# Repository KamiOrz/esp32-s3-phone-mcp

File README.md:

# ESP32-S3 Phone MCP

[English](README.en.md) · [硬件工程](pcb-integrated/README.md) · [MIT License](LICENSE)

**让视觉 AI 通过 Wi-Fi 查看并操作安卓手机。** ESP32-S3 通过 USB ADB 连接手机，在设备上提供带鉴权的 MCP 服务；电脑或云端的多模态 AI 负责理解截图、决定操作，S3 负责执行。

手机无需安装额外应用，需要开启 USB 调试并授权设备。正常操作不依赖电脑上的 ADB 服务，也不依赖单独的 OCR 服务。

## 实拍：已验证的开发板原型

上图是已实测的 **YD-ESP32-23 / ESP32-S3 N16R8 开发板原型**，并非下方集成 PCB 的实物。手机便签中的产品介绍由原型操作输入。照片已移除 EXIF 等元数据。

## 集成 PCB 效果图

- ESP32-S3-WROOM-1-N16R8，独立 CP2102N USB 烧录串口。
- 一个 Type-C 母座接电脑/供电，一个 USB-A 母座接手机，所有焊接引脚为 SMT。
- 55×35mm、四层 PCB，四角 Ø2.2mm M2 固定孔，孔中心距49×29mm。
- 含模组天线伸出部分，组件平面包络约55×41.5mm；外壳还需预留装配和射频净空。
- 输入保护、Type-C 供电能力检测、3.3V 降压与手机端限流保护。

**集成板尚未打样或实板验证。** 当前原理图 ERC、PCB DRC 和一致性检查通过，未连接项为0；这不代表已完成 USB 阻抗、供电浪涌、温升和射频验证。部分3D元件使用简化外形，不能作为精密外壳公差依据。现有固件已在开发板验证，集成板仍需 CC/VBUS 板级适配。未发布制造放行 Gerber。

[KiCad 工程](pcb-integrated/phone-mcp-s3.kicad_pro) · [PCB](pcb-integrated/phone-mcp-s3.kicad_pcb) · [原理图 PDF](pcb-integrated/review/phone-mcp-s3-schematic.pdf) · [BOM](pcb-integrated/BOM.csv) · [检查报告](pcb-integrated/review/STATUS.md)

## 工作原理

```mermaid
flowchart LR
    AI[电脑或云端的视觉 AI] -->|MCP / Wi-Fi| S3[ESP32-S3\n鉴权与命令执行]
    S3 -->|USB Host / ADB| Phone[已授权 USB 调试的安卓手机]
    Phone -->|截图 PNG| S3
    S3 -->|MCP 图片内容| AI
```

截图通过 Wi-Fi 返回给 AI，不经过低速串口。AI 根据截图确定控件位置，调用点击、滑动或应用命令，再截图确认结果。ADB 授权身份在 S3 上使用，每台设备应生成自己的密钥。

## 支持的操作

| 能力 | MCP 工具示例 |
|---|---|
| 查看屏幕与状态 | `phone_screenshot`、`phone_status`、`phone_device_info` |
| 点击、滑动、长按、按键 | `phone_tap`、`phone_swipe`、`phone_long_press`、`phone_keyevent` |
| 应用管理 | `phone_list_apps`、`phone_launch_app`、`phone_stop_app`、`phone_foreground_app` |
| 命令和界面信息 | `phone_adb_shell`、`phone_ui_hierarchy`、`phone_app_info` |
| 唤醒、输入 | `phone_wake_screen`、`phone_input_password`、`phone_input_text` |
| 打开链接 | `phone_open_url` |

当前 MCP 0.4.0 共19个工具。数字 PIN 输入用于输入已知的正确密码，不绕过锁屏；普通文本输入目前仅支持可打印 ASCII。完整参数、返回结构和限制见 [技术说明](README.en.md)。

## 开始使用开发板原型

1. 准备 ESP32-S3 N16R8 开发板、数据线、可用的 USB Host 供电路径，以及已开启 USB 调试的安卓手机。
2. 安装并启用 ESP-IDF 6.1 环境。安卓 platform-tools 仅在本地生成独立 ADB 密钥时需要。
3. 克隆项目并生成本地配置：

```sh
git clone https://github.com/KamiOrz/esp32-s3-phone-mcp.git
cd esp32-s3-phone-mcp
python3 configure_local.py --url http://BOARD_IP/mcp
```

配置脚本交互式读取 Wi-Fi 信息，生成独立 ADB 密钥和 MCP 令牌；配置与密钥文件由 Git 忽略，不会写入公开仓库。

4. 编译烧录（替换串口名）：

```sh
bash hub-probe/build.sh -p /dev/cu.usbserial-PORT -b 460800 build flash
```

5. 在手机上授权设备的 USB 调试请求，然后使用 MCP 客户端连接 `http://BOARD_IP/mcp`，请求头携带 `Authorization: Bearer <本机令牌>`。

命令行测试：

```sh
python3 -m venv .venv
.venv/bin/pip install -r client-requirements.lock.txt
.venv/bin/python phone_cli.py --list
.venv/bin/python phone_cli.py phone_screenshot
.venv/bin/python phone_cli.py phone_launch_app --args '{"package":"com.coloros.calculator"}'
```

开发板的 USB-C 接口不一定支持向手机供电。原型使用板级 USB-OTG 供电改动和 USB Hub，接线应先核对具体开发板的 CC/VBUS 电路；不要把两个电源直接并联。详见[原型接线说明](README.en.md#current-hardware--wiring)。

## 适合什么场景

手机需要离开电脑、固定摆放或通过网络被 AI 调用时，S3 可以作为常驻控制节点。手机就在电脑旁边时，电脑直接连接 ADB 通常更快、功能也更完整。本项目不在 S3 上运行视觉大模型，不提供实时视频流，也不是完整桌面 ADB 的替代品。

当前服务使用局域网 HTTP 和令牌鉴权；不要将手机控制端口直接暴露到公网。手机截图、运行日志、PIN、Wi-Fi 密码和 ADB 私钥都应留在本地。见 [本地数据说明](LOCAL_DATA.md)。

## 目录与许可

- `hub-probe/`：ESP-IDF 固件，USB Host、ADB 与 MCP HTTP 服务。
- `phone_cli.py`、`wifi_client.py`：电脑端调用与截图测试客户端。
- `pcb-integrated/`：KiCad 原理图、PCB、BOM、渲染图和检查报告。
- `docs/images/`：项目实拍图。

原创代码、硬件设计和项目文档/图片按 [MIT](LICENSE) 许可发布，允许按许可证使用、修改与分发。第三方组件保留各自许可证，见 [第三方说明](THIRD_PARTY_NOTICES.md)。

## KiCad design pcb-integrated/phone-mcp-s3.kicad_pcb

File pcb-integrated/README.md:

# Phone MCP S3 集成板 — Rev A1 四层 PCB 评审包

状态：布局与布线完成，含四角 M2 固定孔。原理图 ERC、PCB DRC 与一致性检查通过，未连接为 0。尚未实板验证，不是制造放行版，未输出 Gerber。
目标：替代 YD-ESP32-23 开发板及 Hub，单机连接一台已授权 USB 调试的安卓手机。
用户已确认：ESP32-S3 模组、一个电脑 Type-C 母座、一个手机 USB-A 母座、全贴片焊接。
本目录独立于被忽略的 hardware/，不含网络密码、ADB 私钥、令牌、PIN 或手机数据。

## 1. 架构

```text
现有：电脑 → 开发板 COM         拟设计：电脑 → J1 Type-C
              │                                  ├─USB2 D±→ESD→U2 CP2102N→UART0→U1
          S3 开发板                               ├─CC1/2→U3 TUSB320LAI→供电能力状态→U1
              │                                  └─VBUS→输入保护→5V_SYS
          Hub → 手机                                              ├─U4 Buck→3V3→U1等
                                                                  └─U5 限流/反向保护→J2 VBUS
                                           U1 原生USB GPIO19/20→ESD→J2 USB-A→手机
```

U1：ESP32-S3-WROOM-1-N16R8，保持现有 16MB Flash / 8MB PSRAM 配置。
USB Host 与电脑 USB 串口为两条独立的数据通道，禁止并联。
J2 D+/D- 不短接，不做充电专用口，不宣告快充。
首版不做 PD 高压请求；输入目标是 5V。

## 2. 供电约束与默认策略

电脑端 Type-C 插座不代表电脑必然提供 1.5A/3A。
U3 固定为 UFP/Sink，读取上游默认/1.5A/3A 宣告；不得再并联固定 Rd。
U5 EN 硬件下拉，上电、复位、未读到可靠供电能力时手机 VBUS 关闭。
首版手机端预算目标 500mA，连同主板留出余量，只在检测到至少 1.5A
Type-C 宣告、输入电压正常且固件准备好时使能。
不能把限流典型值当成保证值：需根据 TPS2553 限流上下限选择 RILIM，
当前手机支路 RILIM=44.2kΩ/1%，按厂家公式计算阈值约 531.8–658.8mA，支持500mA正常负载。
输入 eFuse 的 RILM=1.62kΩ/1%，典型阈值约1.25A。仍需验证短路、浪涌、手机电容与线损。
默认电流的老电脑 A 口首先用于刷机/调试；不保证可同时带手机。
USB 枚举前、挂起、掉电等功耗约束仍需在硬件/固件联调验证；
CC 检测本身不等于 USB 枚举授权，不作为 USB 合规结论。

输入保护须落实过压截止/电流限制与输入电容量约束，不能仅靠 TVS
代替过压保护，也不能把所有大电容直接挂在未受控输入 VBUS。
U5 只保护手机支路，不能代替整个板子的输入保护。
5V_SYS 与 PHONE_VBUS 分网；USB-A 端反向灌电不得回到电脑。

## 3. 模组连接分配（已与 KiCad 导出网表核对）

| 功能 | U1 信号 | 说明 |
|---|---|---|
| 手机 USB D- | GPIO19 | 串联阻值按官方指南/实测，靠模组 |
| 手机 USB D+ | GPIO20 | USB Full Speed 12Mbps，成对走线 |
| 烧录 UART TX | GPIO43/U0TXD | 接 U2 RXD |
| 烧录 UART RX | GPIO44/U0RXD | 接 U2 TXD，3.3V 逻辑 |
| 自动下载/复位 | GPIO0、EN | U2 DTR/RTS 经互锁双 NPN 电路；另保留 SMT BOOT/RESET |
| 手机电源开关 | GPIO4 | EN 下拉，启动默认关闭 |
| 手机过流故障 | GPIO5 | 开漏故障输入，3.3V 上拉 |
| CC I2C SDA/SCL | GPIO8/GPIO9 | 3.3V 上拉，确认 U3 上电时序/电平兼容 |
| 状态 LED | GPIO10 | 普通 LED 与串联限流电阻 |
| 预留检测 | GPIO6/GPIO7 | 输入/输出电压分压，防止掉电反供 |

不使用 GPIO35/36/37 等可能被 octal PSRAM 占用的脚。
EN 上拉、复位 RC、GPIO0 上拉与其他启动脚按模组资料审查。
保留 3V3/GND/EN/IO0/TX/RX、两侧 D±、5V_SYS/PHONE_VBUS 测试焊盘。

## 4. 初步机械约束

板框 55×35mm，两接口同侧且开口对齐板边。四角 H1–H4 为 Ø2.2mm NPTH，孔中心距板边3mm、中心距49×29mm；螺丝头按Ø5mm预留双面及内层铜/走线避让。
模组天线位于相对一边，已外伸板边约6.5mm；组件总平面包络因此约55×41.5mm，不能把55×35mm当外壳内尺寸。外壳对应区域不得有金属/电池/螺柱。
模组天线实际禁布范围以官方封装与装壳射频验证为准。
最终改为4层、目标厚度1.6mm FR4：F.Cu为元件/信号及地铜，In1.Cu以GND为主，In2.Cu为信号，B.Cu为信号。In1有一处UART_RST_N局部跨线；需要在板厂叠层确认后进一步复核USB回流与该处地铜连续性。四层制板费用与两层不同。
USB 阻抗按板厂实际叠层计算，不能预先随意指定线宽/间距。
器件尽量顶面贴装；电阻电容以0603为主，QFN/DFN器件采用回流焊。
定位孔、安装孔和过孔可以存在；全贴片指所有焊接引脚（含接口固定脚）为SMT。
外壳需承受USB插拔力，不让固定焊盘单独承力。

## 5. 全贴片器件初选

当前清单见 BOM.csv；BOM-candidates.csv 是最早的选型草案，不作为装配依据。
J1=USB4110-GF-A、J2=UJ2-AH-4-SMT-TR，已依据厂家图核对为全SMT焊接，
J2自建封装的两个1.3mm孔是塑料定位柱孔，不是焊接脚。
L1=XGL4020-472MEC，4.7uH，10%/20%/30%电感下降对应1.9/3.0/4.1A；
C23=T520D157M010ATE055，150uF/10V聚合物，正极接PHONE_VBUS。
U6=TPS259573DSGR，主动低电平OVLO型，不可直接换成同封装其他使能极性版本。
R/C等通用被动器件的具体采购品牌、直流偏压降容及供货仍需在装配BOM冻结时确认。
不能把库存库中“信号SMT、外壳THT”的USB-A母座当全贴片替代。

## 6. 固件影响

现有网络MCP、ADB与截图逻辑可以复用，但不是原固件原样烧录即可发布。
新增 board profile：启动读取CC、管理VBUS EN/故障、欠压关断、恢复状态机。
先检测供电再使能手机VBUS，最后启动USB Host；Wi-Fi状态服务不能无限等待USB枚举，
供电不足时也应能够报告状态。电脑USB默认电流模式需结合CP2102N配置与SUSPEND管脚，
核对枚举前电流、总线电流描述符和挂起策略；不能直接照搬现有固件启动顺序。
不再对USB错误无条件整板重启；电源切换应与USB Host状态同步。
保留本机独立ADB身份生成与本地配置，凭据不进入EDA文件或制造资料。

## 7. 放行检查

- 锁定全部精确MPN、封装焊盘、USB-A纯SMT版本和供货渠道。
- 核对官方参考电路、自动下载真值表与CP2102N VBUS检测分压。
- 电源预算、RILIM公差、输入保护、浪涌、挂起功耗、反灌审查。
- KiCad原理图/ERC、网表审查、PCB走线/DRC与原理图一致性。
- 输出装配图、BOM、坐标、Gerber、钻孔；审核前不称可直接生产。
- 实板验证烧录/Wi-Fi峰值/手机ADB/短路/掉电/重复插拔与连续运行。

## 8. 官方资料

- 模组：https://www.espressif.com/sites/default/files/documentation/esp32-s3-wroom-1_wroom-1u_datasheet_en.pdf
- 设计指南：https://docs.espressif.com/projects/esp-hardware-design-guidelines/en/latest/esp32s3/
- UART：https://www.silabs.com/documents/public/data-sheets/cp2102n-datasheet.pdf
- CP2102N VBUS：https://community.silabs.com/s/article/cp2102n-requires-a-voltage-divider-on-vbus?language=en_US
- CC：https://www.ti.com/lit/ds/symlink/tusb320lai.pdf
- 供电开关：https://www.ti.com/lit/ds/symlink/tps2553.pdf
- Buck：https://www.diodes.com/datasheet/download/AP63200-AP63201-AP63203-AP63205.pdf
- C口纯SMT：https://gct.co/files/info/gct-ionex-usb4110-product-release-booklet.pdf
- A口候选：https://www.sameskydevices.com/product/resource/uj2-ah-smt.pdf

## 9. 当前验证状态

已完成：90个原理图实例（含3个电源标志、4个安装孔）、41个功能网络、234个引脚分配独立核对。
原理图ERC：0错误/0警告；PCB最终DRC：0项违规、0项未连接；原理图一致性：0差异。
PCB有67个贴装器件、16个测试焊盘和4个安装孔；所有焊接引脚为SMT。
最终检查见 `review/final/`，当前文件哈希和机械尺寸见 `review/state.json`。
原有 `review/pcb-current/` 是A0预布局的历史报告，不代表当前版本。
全页自动视觉评分曾在重复标签匹配阶段中断，不计为通过；原理图PDF/SVG可供审阅。

尚未完成：板厂叠层/USB阻抗与回流复核、制造文件冻结、固件适配及实板测试。
不承诺当前USB几何已经达到90Ω；DRC通过不等于USB合规、电源浪涌或射频测试通过。
部分过孔位于焊盘附近/焊盘内，装配厂需评估吸锡、塞孔和工艺要求；不能据此直接量产。

## 10. 文件入口与重建

- phone-mcp-s3.kicad_pro：KiCad 10工程入口。
- phone-mcp-s3.kicad_sch：正式可编辑原理图（A1审阅版）。
- phone-mcp-s3.kicad_pcb：55×35mm、4层、已布线，四角M2安装孔。
- review/phone-mcp-s3-schematic.pdf：原理图PDF。
- review/erc.rpt：原理图ERC；review/final/drc.rpt为JSON格式最终检查。
- review/connectivity-check.json：独立网表检查及限流计算。
- review/STATUS.md：本次交付边界和待办。
- review/pcb-3d-top.png / pcb-3d-isometric.png：实际KiCad板文件生成的渲染；五个器件使用简化外形，详见models/README.md。

项目生成器通过 `kicad-tool project-build` 调用结构化API；不要手工编辑EDA文件。
以下命令只重建原理图和初始布局，**会覆盖最终布线，不能用来复现最终走线**。修改前应另存或使用Git分支。最终走线以已提交的KiCad板文件为准。

```sh
python3 tools/make_spec.py
kicad-tool project-build tools/build_footprints.py --dry-run
kicad-tool project-build tools/build_footprints.py
kicad-tool project-build tools/build_design.py --dry-run
kicad-tool project-build tools/build_design.py
kicad-tool project-build tools/export_review.py
kicad-tool project-build tools/build_board.py --dry-run
kicad-tool project-build tools/build_board.py
python3 tools/configure_project.py
kicad-tool sch erc phone-mcp-s3.kicad_sch -o review/erc.rpt
```

生成器当前使用macOS的KiCad安装路径；工程文件可在安装标准库的其他KiCad 10平台打开。
厂家PDF保存在本机references/并被Git忽略，网络资料入口见上文。未把设计提交至在线EDA或云布线服务。

重新检查及渲染现有最终板文件（不重建布局）：

```sh
kicad-tool pcb validate phone-mcp-s3.kicad_pcb phone-mcp-s3.kicad_sch --save-baseline review/final
kicad-tool project-build tools/finish_board.py audit
kicad-tool project-build tools/finish_board.py render
```

渲染依赖KiCad自带3D库与项目models目录；USB接口等简化模型只表达外形包络，不是外壳公差依据。

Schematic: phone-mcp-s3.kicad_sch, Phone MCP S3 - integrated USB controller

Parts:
C1, C19, C20: 22u/6.3V X7R; C_0805_2012Metric
C2, C4: 1u/10V X7R; C_0603_1608Metric
C3, C6, C8, C9, C10, C11, C21: 100n/10V X7R; C_0603_1608Metric
C5, C7: 4.7u/10V X7R; C_0603_1608Metric
C12: 1u/25V X7R; C_0603_1608Metric
C13, C16, C17, C22, C24: 100n/25V X7R; C_0603_1608Metric
C14: 10n/25V C0G; C_0603_1608Metric
C15, C18: 10u/10V X7R; C_0805_2012Metric
C23: 150u/10V low-ESR; CP_EIA-7343-31_Kemet-D; MPN T520D157M010ATE055
D1: GREEN; LED_0603_1608Metric
D2: SMF6.0A; D_SMF; MPN SMF6.0A
H1, H2, H3, H4: M2 NPTH 2.2mm; MountingHole_2.2mm_M2
J1: USB4110-GF-A; USB_C_Receptacle_GCT_USB4110; MPN USB4110-GF-A
J2: UJ2-AH-4-SMT-TR; USB_A_SameSky_UJ2_AH_SMT; MPN UJ2-AH-4-SMT-TR
L1: 4.7uH XGL4020; L_Coilcraft_XGL4020; MPN XGL4020-472MEC
Q1, Q2: MMBT3904; SOT-23; MPN MMBT3904-7-F
R1, R2, R7, R8, R12, R20, R22, R23: 10k 1%; R_0603_1608Metric
R3, R4: 1k 1%; R_0603_1608Metric
R5: 22.1k 1%; R_0603_1608Metric
R6: 47.5k 1%; R_0603_1608Metric
R9: 887k 1%; R_0603_1608Metric
R10, R11: 4.7k 1%; R_0603_1608Metric
R13, R15: 330k 1%; R_0603_1608Metric
R14, R16: 100k 1%; R_0603_1608Metric
R17: 367k 0.1%; R_0603_1608Metric
R18: 100k 0.1%; R_0603_1608Metric
R19: 1.62k 1%; R_0603_1608Metric
R21: 44.2k 1%; R_0603_1608Metric
R24, R25: 22R 1%; R_0603_1608Metric
SW1: RESET; SW_SPST_PTS810; MPN PTS810 SJM 250 SMTR LFS
SW2: BOOT; SW_SPST_PTS810; MPN PTS810 SJM 250 SMTR LFS
TP1: GND; TestPoint_Pad_D1.0mm
TP2: 3V3; TestPoint_Pad_D1.0mm
TP3: VBUS_RAW; TestPoint_Pad_D1.0mm
TP4: 5V_SYS; TestPoint_Pad_D1.0mm
TP5: PHONE_VBUS; TestPoint_Pad_D1.0mm
TP6: ESP_EN; TestPoint_Pad_D1.0mm
TP7: BOOT_N; TestPoint_Pad_D1.0mm
TP8: ESP_TX; TestPoint_Pad_D1.0mm
TP9: ESP_RX; TestPoint_Pad_D1.0mm
TP10: PHONE_EN; TestPoint_Pad_D1.0mm
TP11: PHONE_FAULT_N; TestPoint_Pad_D1.0mm
TP12: CC_SDA; TestPoint_Pad_D1.0mm
TP13: CC_SCL; TestPoint_Pad_D1.0mm
TP14: CC_INT_N; TestPoint_Pad_D1.0mm
TP15: INPUT_FAULT_N; TestPoint_Pad_D1.0mm
TP16: PC_SUSPEND; TestPoint_Pad_D1.0mm
U1: ESP32-S3-WROOM-1-N16R8; ESP32_S3_WROOM_1_Overhang; MPN ESP32-S3-WROOM-1-N16R8
U2: CP2102N-A02-GQFN24R; QFN-24-1EP_4x4mm_P0.5mm_EP2.6x2.6mm; MPN CP2102N-A02-GQFN24R
U3: TUSB320LAIRWBR; Texas_X2QFN-12_1.6x1.6mm_P0.4mm; MPN TUSB320LAIRWBR
U4: AP63203WU-7; TSOT-23-6; MPN AP63203WU-7
U5: TPS2553DBVR; SOT-23-6; MPN TPS2553DBVR
U6: TPS259573DSGR; DFN-8-1EP_2x2mm_P0.5mm_EP0.9x1.6mm; MPN TPS259573DSGR
U7, U8, U9: USBLC6-2SC6; SOT-23-6; MPN USBLC6-2SC6

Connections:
/3V3: C1.1, C2.1, C3.1, C5.1, C6.1, C7.1, C8.1, C9.1, C19.1, C20.1, C21.1, D1.2 (A), L1.2, R1.1, R2.1, R4.1, R10.1, R11.1, R12.1, R20.1, R23.1, TP2.1, U1.2 (3V3), U2.5 (VIO), U2.6 (VDD), U2.7 (VREGIN), U3.12 (VDD), U4.1 (FB)
/5V_SYS: C15.1, C16.1, C18.1, C22.1, TP4.1, U4.2 (EN), U4.3 (IN), U5.1 (IN), U6.5 (OUT), U7.5 (VBUS), U9.5 (VBUS)
/BOOT_N: Q2.3 (C), R2.2, SW2.1, TP7.1, U1.27 (IO0)
/BUCK_BST: C17.1, U4.6 (BST)
/BUCK_SW: C17.2, L1.1, U4.5 (SW)
/CC1: J1.A5 (CC1), U3.1 (CC1), U9.1 (I/O1), U9.6 (I/O1)
/CC2: J1.B5 (CC2), U3.2 (CC2), U9.3 (I/O2), U9.4 (I/O2)
/CC_INT_N: R12.2, TP14.1, U1.20 (IO12), U3.6 (~INT/OUT3)
/CC_SCL: R11.2, TP13.1, U1.17 (IO9), U3.8 (SCL/OUT2)
/CC_SDA: R10.2, TP12.1, U1.12 (IO8), U3.7 (SDA/OUT1)
/CC_VBUS_DET: R9.2, U3.4 (VBUS_DET)
/ESP_EN: C4.1, Q1.3 (C), R1.2, SW1.1, TP6.1, U1.3 (EN)
/ESP_RX: TP9.1, U1.36 (RXD0), U2.21 (TXD)
/ESP_TX: TP8.1, U1.37 (TXD0), U2.20 (RXD)
/ESP_USB_DM: R24.1, U1.13 (USB_D-)
/ESP_USB_DP: R25.1, U1.14 (USB_D+)
/GND: C1.2, C2.2, C3.2, C4.2, C5.2, C6.2, C7.2, C8.2, C9.2, C10.2, C11.2, C12.2, C13.2, C14.2, C15.2, C16.2, C18.2, C19.2, C20.2, C21.2, C22.2, C23.2, C24.2, D2.2 (A), J1.A1 (GND), J1.A12 (GND), J1.B1 (GND), J1.B12 (GND), J1.SH (SHIELD), J2.4 (GND), J2.SH (Shield), R6.2, R14.2, R16.2, R18.2, R19.2, R21.2, R22.2, SW1.2, SW2.2, TP1.1, U1.1 (GND), U1.40 (GND), U1.41 (GND), U2.2 (GND), U2.25 (GND), U3.3 (PORT), U3.5 (ADDR), U3.10 (GND), U3.11 (~EN), U4.4 (GND), U5.2 (GND), U6.8 (GND), U6.9 (EP/GND), U7.2 (GND), U8.2 (GND), U9.2 (GND)
/INPUT_DVDT: C14.1, U6.1 (dVdt)
/INPUT_FAULT_N: R20.2, TP15.1, U1.21 (IO13), U6.6 (~FLT)
/INPUT_ILIM: R19.1, U6.7 (ILM)
/INPUT_OVLO: R17.2, R18.1, U6.2 (EN/OVLO)
/LED_K: D1.1 (K), R3.2
/PC_DM: J1.A7 (D-), J1.B7 (D-), U2.4 (D-), U7.1 (I/O1), U7.6 (I/O1)
/PC_DP: J1.A6 (D+), J1.B6 (D+), U2.3 (D+), U7.3 (I/O2), U7.4 (I/O2)
/PC_SUSPEND: TP16.1, U1.19 (IO11), U2.17 (SUSPEND)
/PC_VBUS_DET: R5.2, R6.1, U2.8 (VBUS)
/PHONE_DM: J2.2 (D-), R24.2, U8.1 (I/O1), U8.6 (I/O1)
/PHONE_DP: J2.3 (D+), R25.2, U8.3 (I/O2), U8.4 (I/O2)
/PHONE_EN: R22.1, TP10.1, U1.4 (IO4), U5.3 (EN)
/PHONE_FAULT_N: R23.2, TP11.1, U1.5 (IO5), U5.4 (~FAULT)
/PHONE_ILIM: R21.1, U5.5 (ILIM)
/PHONE_SENSE: C11.1, R15.2, R16.1, U1.7 (IO7)
/PHONE_VBUS: C23.1, C24.1, J2.1 (VBUS), R15.1, TP5.1, U5.6 (OUT), U8.5 (VBUS)
/Q_BOOT_B: Q2.1 (B), R8.2
/Q_RESET_B: Q1.1 (B), R7.2
/STATUS_LED: R3.1, U1.18 (IO10)
/UART_DTR: Q2.2 (E), R7.1, U2.23 (~DTR)
/UART_RST_N: R4.2, U2.9 (~RST)
/UART_RTS: Q1.2 (E), R8.1, U2.19 (~RTS)
/VBUS_RAW: C12.1, C13.1, D2.1 (K), J1.A4 (VBUS), J1.A9 (VBUS), J1.B4 (VBUS), J1.B9 (VBUS), R5.1, R9.1, R13.1, R17.1, TP3.1, U6.3 (IN), U6.4 (IN)
/VIN_SENSE: C10.1, R13.2, R14.1, U1.6 (IO6)

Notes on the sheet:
01 ESP32-S3 / reset / status
02 PC USB UART / auto download
03 Type-C sink / power sensing
04 PC USB-C / ESD / input
05 Input eFuse / controlled inrush
06 3.3V switching supply
07 Phone power / default OFF
08 Android USB-A / USB FS
PRIVATE - A1 PCB REVIEW - NO MANUFACTURING RELEASE
NC on unused GPIO is intentional. IO35/36/37 reserved for module PSRAM.
U3 PORT=GND: UFP; ADDR=GND: 0x47; EN_N=GND; internal Rd only.
AUTO RESET: DTR/RTS 00 or 11 -> EN/BOOT both high; 10 -> reset; 01 -> boot low.
Firmware must verify >=1.5A source before PHONE_EN. 44.2k limit approximately 0.53-0.66A.

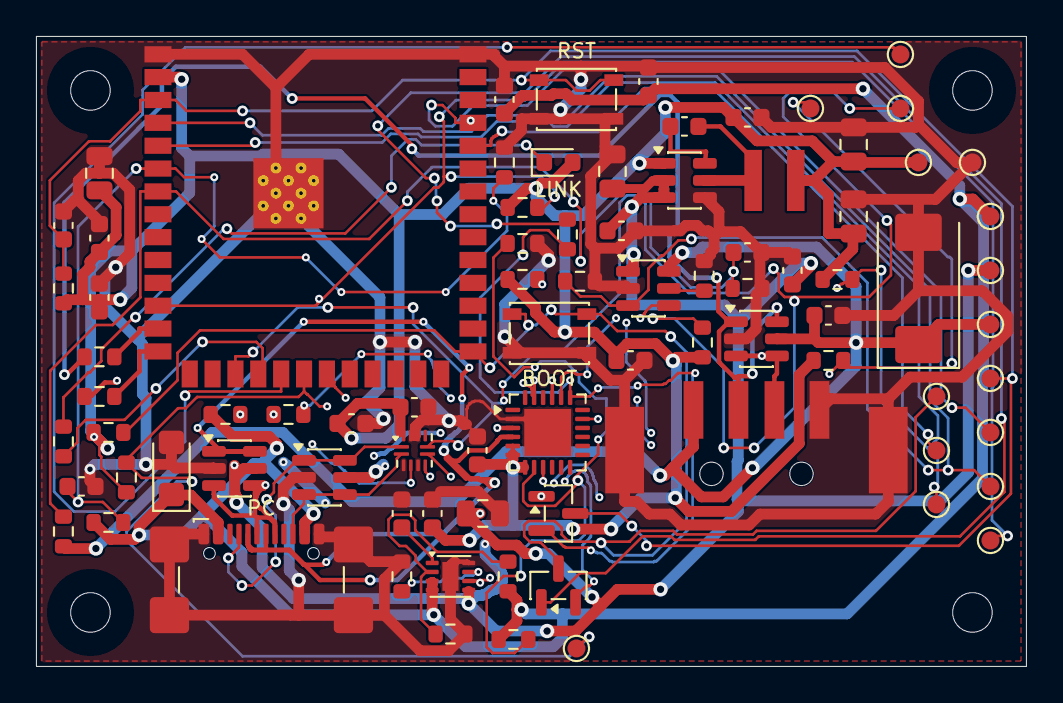
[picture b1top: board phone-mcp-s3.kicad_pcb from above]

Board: 4 copper layers, 55.0 x 35.0 mm, 87 parts (0 on the bottom side), 41 nets.

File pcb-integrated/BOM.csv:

Reference,Value,Footprint,MPN
U1,ESP32-S3-WROOM-1-N16R8,PhoneMCP:ESP32_S3_WROOM_1_Overhang,ESP32-S3-WROOM-1-N16R8
C1,22u/6.3V X7R,Capacitor_SMD:C_0805_2012Metric,
C2,1u/10V X7R,Capacitor_SMD:C_0603_1608Metric,
C3,100n/10V X7R,Capacitor_SMD:C_0603_1608Metric,
R1,10k 1%,Resistor_SMD:R_0603_1608Metric,
C4,1u/10V X7R,Capacitor_SMD:C_0603_1608Metric,
R2,10k 1%,Resistor_SMD:R_0603_1608Metric,
SW1,RESET,Button_Switch_SMD:SW_SPST_PTS810,PTS810 SJM 250 SMTR LFS
SW2,BOOT,Button_Switch_SMD:SW_SPST_PTS810,PTS810 SJM 250 SMTR LFS
R3,1k 1%,Resistor_SMD:R_0603_1608Metric,
D1,GREEN,LED_SMD:LED_0603_1608Metric,
U2,CP2102N-A02-GQFN24R,Package_DFN_QFN:QFN-24-1EP_4x4mm_P0.5mm_EP2.6x2.6mm,CP2102N-A02-GQFN24R
C5,4.7u/10V X7R,Capacitor_SMD:C_0603_1608Metric,
C6,100n/10V X7R,Capacitor_SMD:C_0603_1608Metric,
C7,4.7u/10V X7R,Capacitor_SMD:C_0603_1608Metric,
C8,100n/10V X7R,Capacitor_SMD:C_0603_1608Metric,
R4,1k 1%,Resistor_SMD:R_0603_1608Metric,
R5,22.1k 1%,Resistor_SMD:R_0603_1608Metric,
R6,47.5k 1%,Resistor_SMD:R_0603_1608Metric,
R7,10k 1%,Resistor_SMD:R_0603_1608Metric,
R8,10k 1%,Resistor_SMD:R_0603_1608Metric,
Q1,MMBT3904,Package_TO_SOT_SMD:SOT-23,MMBT3904-7-F
Q2,MMBT3904,Package_TO_SOT_SMD:SOT-23,MMBT3904-7-F
U3,TUSB320LAIRWBR,Package_DFN_QFN:Texas_X2QFN-12_1.6x1.6mm_P0.4mm,TUSB320LAIRWBR
C9,100n/10V X7R,Capacitor_SMD:C_0603_1608Metric,
R9,887k 1%,Resistor_SMD:R_0603_1608Metric,
R10,4.7k 1%,Resistor_SMD:R_0603_1608Metric,
R11,4.7k 1%,Resistor_SMD:R_0603_1608Metric,
R12,10k 1%,Resistor_SMD:R_0603_1608Metric,
R13,330k 1%,Resistor_SMD:R_0603_1608Metric,
R14,100k 1%,Resistor_SMD:R_0603_1608Metric,
C10,100n/10V X7R,Capacitor_SMD:C_0603_1608Metric,
R15,330k 1%,Resistor_SMD:R_0603_1608Metric,
R16,100k 1%,Resistor_SMD:R_0603_1608Metric,
C11,100n/10V X7R,Capacitor_SMD:C_0603_1608Metric,
J1,USB4110-GF-A,Connector_USB:USB_C_Receptacle_GCT_USB4110,USB4110-GF-A
C12,1u/25V X7R,Capacitor_SMD:C_0603_1608Metric,
C13,100n/25V X7R,Capacitor_SMD:C_0603_1608Metric,
D2,SMF6.0A,Diode_SMD:D_SMF,SMF6.0A
U7,USBLC6-2SC6,Package_TO_SOT_SMD:SOT-23-6,USBLC6-2SC6
U9,USBLC6-2SC6,Package_TO_SOT_SMD:SOT-23-6,USBLC6-2SC6
U6,TPS259573DSGR,Package_DFN_QFN:DFN-8-1EP_2x2mm_P0.5mm_EP0.9x1.6mm,TPS259573DSGR
R17,367k 0.1%,Resistor_SMD:R_0603_1608Metric,
R18,100k 0.1%,Resistor_SMD:R_0603_1608Metric,
R19,1.62k 1%,Resistor_SMD:R_0603_1608Metric,
C14,10n/25V C0G,Capacitor_SMD:C_0603_1608Metric,
R20,10k 1%,Resistor_SMD:R_0603_1608Metric,
C15,10u/10V X7R,Capacitor_SMD:C_0805_2012Metric,
C16,100n/25V X7R,Capacitor_SMD:C_0603_1608Metric,
U4,AP63203WU-7,Package_TO_SOT_SMD:TSOT-23-6,AP63203WU-7
L1,4.7uH XGL4020,PhoneMCP:L_Coilcraft_XGL4020,XGL4020-472MEC
C17,100n/25V X7R,Capacitor_SMD:C_0603_1608Metric,
C18,10u/10V X7R,Capacitor_SMD:C_0805_2012Metric,
C19,22u/6.3V X7R,Capacitor_SMD:C_0805_2012Metric,
C20,22u/6.3V X7R,Capacitor_SMD:C_0805_2012Metric,
C21,100n/10V X7R,Capacitor_SMD:C_0603_1608Metric,
U5,TPS2553DBVR,Package_TO_SOT_SMD:SOT-23-6,TPS2553DBVR
R21,44.2k 1%,Resistor_SMD:R_0603_1608Metric,
R22,10k 1%,Resistor_SMD:R_0603_1608Metric,
R23,10k 1%,Resistor_SMD:R_0603_1608Metric,
C22,100n/25V X7R,Capacitor_SMD:C_0603_1608Metric,
C23,150u/10V low-ESR,Capacitor_Tantalum_SMD:CP_EIA-7343-31_Kemet-D,T520D157M010ATE055
C24,100n/25V X7R,Capacitor_SMD:C_0603_1608Metric,
R24,22R 1%,Resistor_SMD:R_0603_1608Metric,
R25,22R 1%,Resistor_SMD:R_0603_1608Metric,
J2,UJ2-AH-4-SMT-TR,PhoneMCP:USB_A_SameSky_UJ2_AH_SMT,UJ2-AH-4-SMT-TR
U8,USBLC6-2SC6,Package_TO_SOT_SMD:SOT-23-6,USBLC6-2SC6
TP1,GND,TestPoint:TestPoint_Pad_D1.0mm,
TP2,3V3,TestPoint:TestPoint_Pad_D1.0mm,
TP3,VBUS_RAW,TestPoint:TestPoint_Pad_D1.0mm,
TP4,5V_SYS,TestPoint:TestPoint_Pad_D1.0mm,
TP5,PHONE_VBUS,TestPoint:TestPoint_Pad_D1.0mm,
TP6,ESP_EN,TestPoint:TestPoint_Pad_D1.0mm,
TP7,BOOT_N,TestPoint:TestPoint_Pad_D1.0mm,
TP8,ESP_TX,TestPoint:TestPoint_Pad_D1.0mm,
TP9,ESP_RX,TestPoint:TestPoint_Pad_D1.0mm,
TP10,PHONE_EN,TestPoint:TestPoint_Pad_D1.0mm,
TP11,PHONE_FAULT_N,TestPoint:TestPoint_Pad_D1.0mm,
TP12,CC_SDA,TestPoint:TestPoint_Pad_D1.0mm,
TP13,CC_SCL,TestPoint:TestPoint_Pad_D1.0mm,
TP14,CC_INT_N,TestPoint:TestPoint_Pad_D1.0mm,
TP15,INPUT_FAULT_N,TestPoint:TestPoint_Pad_D1.0mm,
TP16,PC_SUSPEND,TestPoint:TestPoint_Pad_D1.0mm,
H1,M2 NPTH 2.2mm,MountingHole:MountingHole_2.2mm_M2,
H2,M2 NPTH 2.2mm,MountingHole:MountingHole_2.2mm_M2,
H3,M2 NPTH 2.2mm,MountingHole:MountingHole_2.2mm_M2,
H4,M2 NPTH 2.2mm,MountingHole:MountingHole_2.2mm_M2,
